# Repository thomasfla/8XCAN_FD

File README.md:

# 8XCAN_FD
8 SPI MCP2517FD chip on the same SPI bus using a single quartz. Eagle board design files and Arduino sketch to use it

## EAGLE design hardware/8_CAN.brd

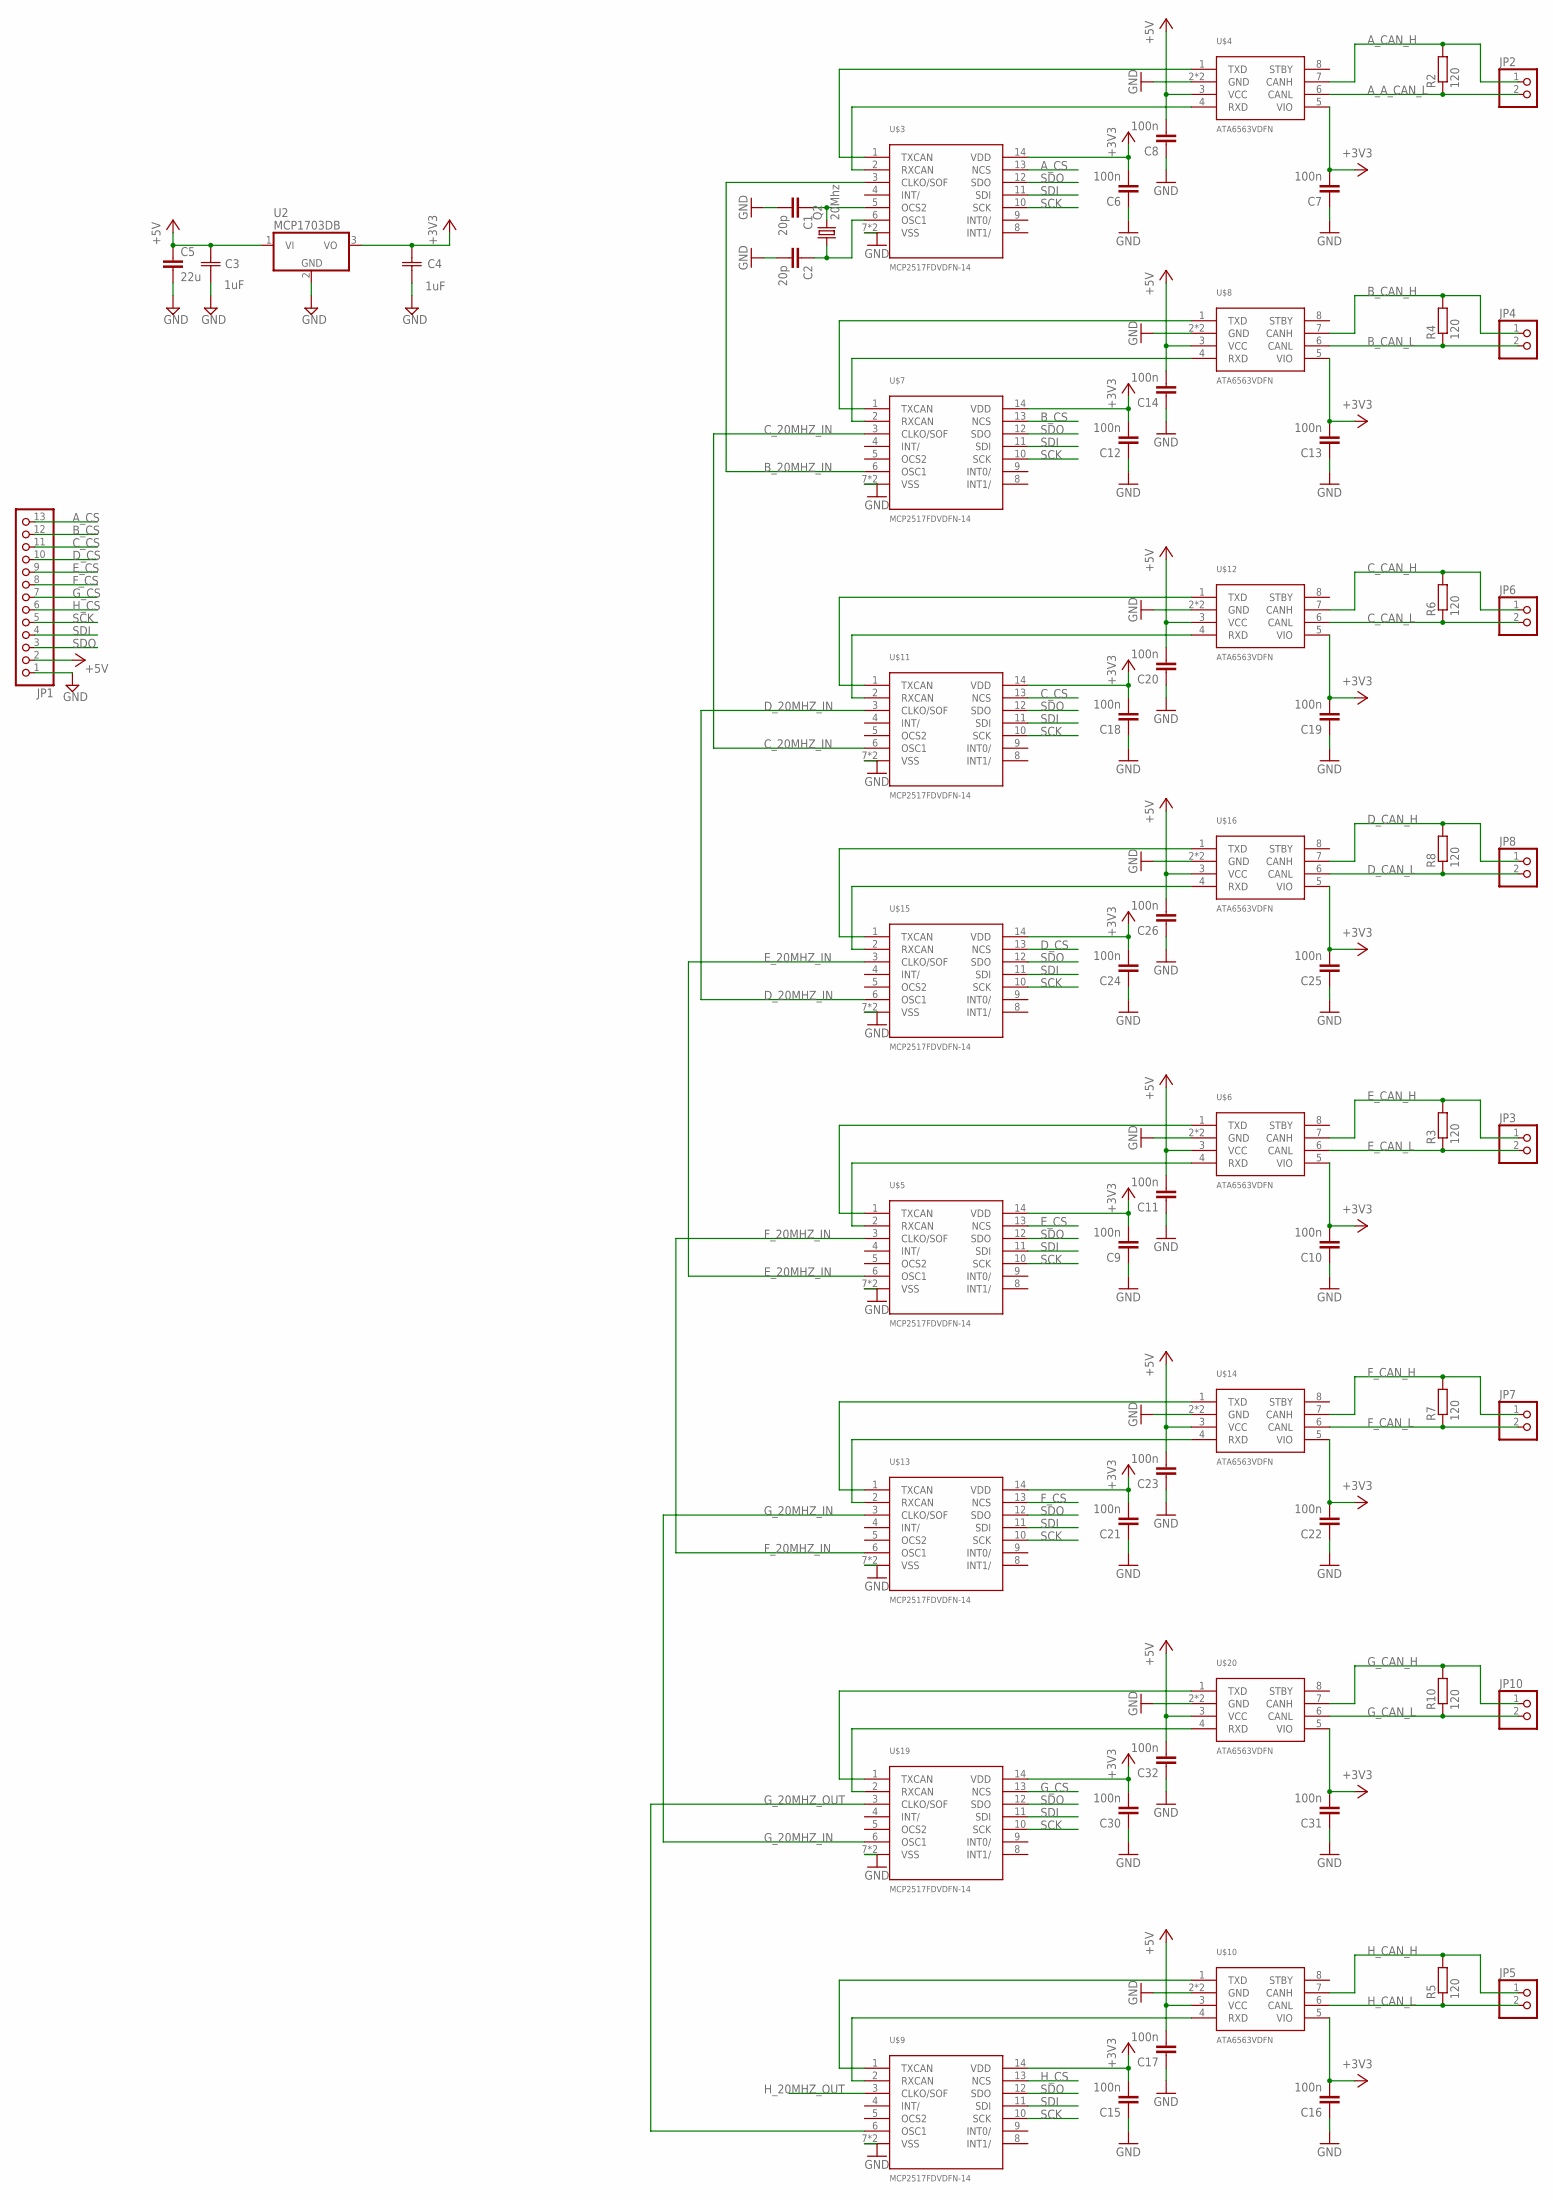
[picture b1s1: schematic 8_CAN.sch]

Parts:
C1, C2: 20p; C0402
C3, C4: 1uF; CAPC2013X140N
C5: 22u; C1206
C6, C7, C8, C9, C10, C11, C12, C13, C14, C15, C16, C17, C18, C19, C20, C21, C22, C23, C24, C25, C26, C30, C31, C32: 100n; C0402
JP1: PINHD-1X13; 1X13
JP2, JP3, JP4, JP5, JP6, JP7, JP8, JP10: PINHD-1X2; 1X02
Q2: 20Mhz; CTS406
R2, R3, R4, R5, R6, R7, R8, R10: 120; R0402
U2: MCP1703DB; SOT223
U$3, U$5, U$7, U$9, U$11, U$13, U$15, U$19: MCP2517FDVDFN-14; VDFN-14_4.5X3
U$4, U$6, U$8, U$10, U$12, U$14, U$16, U$20: ATA6563VDFN; VDFN-8_3X3

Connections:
+3V3: C4.1 (C1), C6.2, C7.2, C9.2, C10.2, C12.2, C13.2, C15.2, C16.2, C18.2, C19.2, C21.2, C22.2, C24.2, C25.2, C30.2, C31.2, U2.3 (VO), U$3.14 (VDD), U$4.5 (VIO), U$5.14 (VDD), U$6.5 (VIO), U$7.14 (VDD), U$8.5 (VIO), U$9.14 (VDD), U$10.5 (VIO), U$11.14 (VDD), U$12.5 (VIO), U$13.14 (VDD), U$14.5 (VIO), U$15.14 (VDD), U$16.5 (VIO), U$19.14 (VDD), U$20.5 (VIO)
+5V: C3.1 (C1), C5.1, C8.2, C11.2, C14.2, C17.2, C20.2, C23.2, C26.2, C32.2, JP1.2, U2.1 (VI), U$4.3 (VCC), U$6.3 (VCC), U$8.3 (VCC), U$10.3 (VCC), U$12.3 (VCC), U$14.3 (VCC), U$16.3 (VCC), U$20.3 (VCC)
A_A_CAN_L: JP2.2, R2.1, U$4.6 (CANL)
A_CAN_H: JP2.1, R2.2, U$4.7 (CANH)
A_CS: JP1.13, U$3.13 (NCS)
B_20MHZ_IN: U$3.3 (CLKO/SOF), U$7.6 (OSC1)
B_CAN_H: JP4.1, R4.2, U$8.7 (CANH)
B_CAN_L: JP4.2, R4.1, U$8.6 (CANL)
B_CS: JP1.12, U$7.13 (NCS)
C_20MHZ_IN: U$7.3 (CLKO/SOF), U$11.6 (OSC1)
C_CAN_H: JP6.1, R6.2, U$12.7 (CANH)
C_CAN_L: JP6.2, R6.1, U$12.6 (CANL)
C_CS: JP1.11, U$11.13 (NCS)
D_20MHZ_IN: U$11.3 (CLKO/SOF), U$15.6 (OSC1)
D_CAN_H: JP8.1, R8.2, U$16.7 (CANH)
D_CAN_L: JP8.2, R8.1, U$16.6 (CANL)
D_CS: JP1.10, U$15.13 (NCS)
E_20MHZ_IN: U$5.6 (OSC1), U$15.3 (CLKO/SOF)
E_CAN_H: JP3.1, R3.2, U$6.7 (CANH)
E_CAN_L: JP3.2, R3.1, U$6.6 (CANL)
E_CS: JP1.9, U$5.13 (NCS)
F_20MHZ_IN: U$5.3 (CLKO/SOF), U$13.6 (OSC1)
F_CAN_H: JP7.1, R7.2, U$14.7 (CANH)
F_CAN_L: JP7.2, R7.1, U$14.6 (CANL)
F_CS: JP1.8, U$13.13 (NCS)
GND: C1.2, C2.2, C3.2 (C2), C4.2 (C2), C5.2, C6.1, C7.1, C8.1, C9.1, C10.1, C11.1, C12.1, C13.1, C14.1, C15.1, C16.1, C17.1, C18.1, C19.1, C20.1, C21.1, C22.1, C23.1, C24.1, C25.1, C26.1, C30.1, C31.1, C32.1, JP1.1, U2.2 (GND), U$3.7 (VSS), U$3.15 (VSS), U$4.2 (GND), U$4.9 (GND), U$5.7 (VSS), U$5.15 (VSS), U$6.2 (GND), U$6.9 (GND), U$7.7 (VSS), U$7.15 (VSS), U$8.2 (GND), U$8.9 (GND), U$9.7 (VSS), U$9.15 (VSS), U$10.2 (GND), U$10.9 (GND), U$11.7 (VSS), U$11.15 (VSS), U$12.2 (GND), U$12.9 (GND), U$13.7 (VSS), U$13.15 (VSS), U$14.2 (GND), U$14.9 (GND), U$15.7 (VSS), U$15.15 (VSS), U$16.2 (GND), U$16.9 (GND), U$19.7 (VSS), U$19.15 (VSS), U$20.2 (GND), U$20.9 (GND)
G_20MHZ_IN: U$13.3 (CLKO/SOF), U$19.6 (OSC1)
G_20MHZ_OUT: U$9.6 (OSC1), U$19.3 (CLKO/SOF)
G_CAN_H: JP10.1, R10.2, U$20.7 (CANH)
G_CAN_L: JP10.2, R10.1, U$20.6 (CANL)
G_CS: JP1.7, U$19.13 (NCS)
H_20MHZ_OUT: U$9.3 (CLKO/SOF)
H_CAN_H: JP5.1, R5.2, U$10.7 (CANH)
H_CAN_L: JP5.2, R5.1, U$10.6 (CANL)
H_CS: JP1.6, U$9.13 (NCS)
unnamed: C1.1, Q2.3 (2), U$3.5 (OCS2)
unnamed: C2.1, Q2.1, U$3.6 (OSC1)
unnamed: U$3.1 (TXCAN), U$4.1 (TXD)
unnamed: U$3.2 (RXCAN), U$4.4 (RXD)
unnamed: U$5.1 (TXCAN), U$6.1 (TXD)
unnamed: U$5.2 (RXCAN), U$6.4 (RXD)
unnamed: U$7.1 (TXCAN), U$8.1 (TXD)
unnamed: U$7.2 (RXCAN), U$8.4 (RXD)
unnamed: U$9.1 (TXCAN), U$10.1 (TXD)
unnamed: U$9.2 (RXCAN), U$10.4 (RXD)
unnamed: U$11.1 (TXCAN), U$12.1 (TXD)
unnamed: U$11.2 (RXCAN), U$12.4 (RXD)
unnamed: U$13.1 (TXCAN), U$14.1 (TXD)
unnamed: U$13.2 (RXCAN), U$14.4 (RXD)
unnamed: U$15.1 (TXCAN), U$16.1 (TXD)
unnamed: U$15.2 (RXCAN), U$16.4 (RXD)
unnamed: U$19.1 (TXCAN), U$20.1 (TXD)
unnamed: U$19.2 (RXCAN), U$20.4 (RXD)
SCK: JP1.5, U$3.10 (SCK), U$5.10 (SCK), U$7.10 (SCK), U$9.10 (SCK), U$11.10 (SCK), U$13.10 (SCK), U$15.10 (SCK), U$19.10 (SCK)
SDI: JP1.4, U$3.11 (SDI), U$5.11 (SDI), U$7.11 (SDI), U$9.11 (SDI), U$11.11 (SDI), U$13.11 (SDI), U$15.11 (SDI), U$19.11 (SDI)
SDO: JP1.3, U$3.12 (SDO), U$5.12 (SDO), U$7.12 (SDO), U$9.12 (SDO), U$11.12 (SDO), U$13.12 (SDO), U$15.12 (SDO), U$19.12 (SDO)

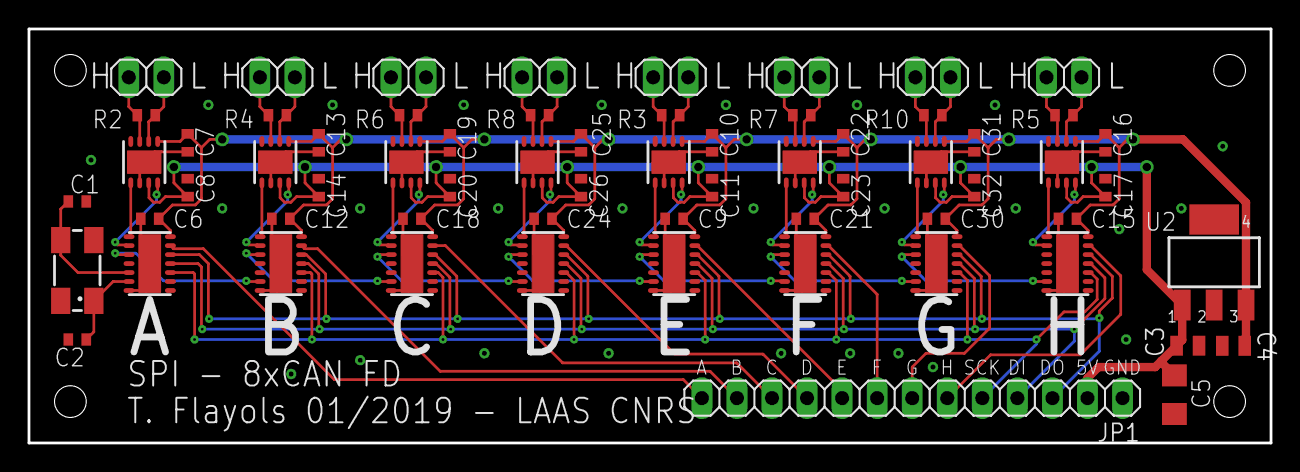
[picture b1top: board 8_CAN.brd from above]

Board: 2 copper layers, 90.0 x 30.0 mm, 64 parts (0 on the bottom side), 55 nets.

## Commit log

2019-02-06 add eagle design files
2019-02-06 Working example using CAN_A and CAN_B in loopback mode
2019-02-07 extend to 8 CAN
